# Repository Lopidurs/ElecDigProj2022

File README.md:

# ElecDigProj2022
Projet d'électronique digitale : Programmation d'un PIC18F458 pour mesurer une distance avec un HC-SR04

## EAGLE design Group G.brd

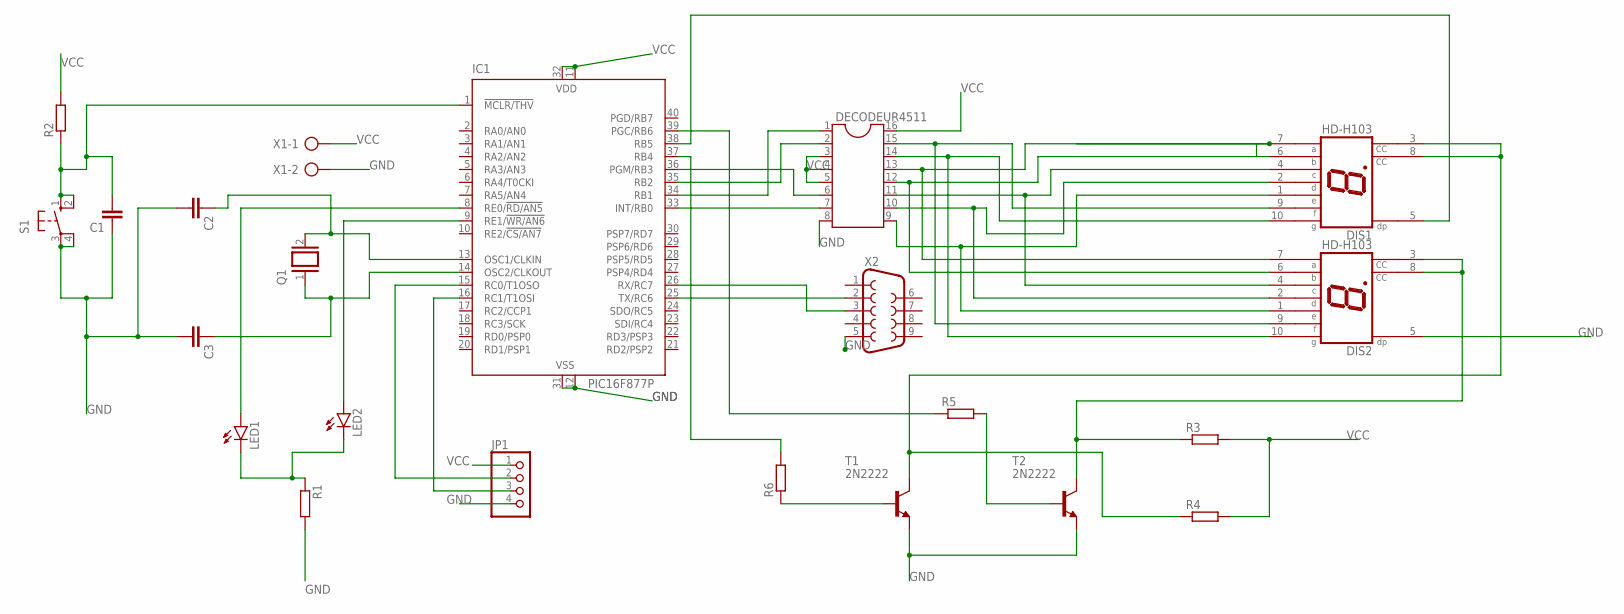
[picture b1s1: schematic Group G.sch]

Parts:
C1, C2, C3: C-EU025-025X050; C025-025X050
DECODEUR4511: DIL16
DIS1, DIS2: HD-H103; HDSP-M
IC1: PIC16F877P; DIL40
JP1: PINHD-1X4; 1X04
LED1, LED2: LED5MM
Q1: XTAL/S; QS
R1, R2, R3, R4, R5, R6: R-EU_0207/10; 0207/10
S1: 10-XX; B3F-10XX
T1, T2: 2N2222; TO18
X1: AK300/2
X2: F09H

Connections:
GND: C1.1, C2.2, C3.2, DECODEUR4511.8, DIS2.5 (DP), IC1.12 (VSS), IC1.31 (VSS), JP1.4, R1.2, S1.3, S1.4 (P1), T1.1 (E), T2.1 (E), X1.2, X2.5
unnamed: IC1.25 (TX/RC6), X2.2
unnamed: IC1.26 (RX/RC7), X2.3
unnamed: DECODEUR4511.7, IC1.33 (INT/RB0)
unnamed: DECODEUR4511.1, IC1.34 (RB1)
unnamed: DECODEUR4511.2, IC1.35 (RB2)
unnamed: DECODEUR4511.6, IC1.36 (PGM/RB3)
unnamed: DECODEUR4511.13, DIS1.7 (A), DIS2.7 (A)
unnamed: DECODEUR4511.15, DIS1.9 (F), DIS2.9 (F)
unnamed: DECODEUR4511.14, DIS1.10 (G), DIS2.10 (G)
unnamed: DECODEUR4511.10, DIS1.2 (D), DIS2.2 (D)
unnamed: DECODEUR4511.12, DIS1.6 (B), DIS2.6 (B)
unnamed: DECODEUR4511.11, DIS1.4 (C), DIS2.4 (C)
unnamed: DECODEUR4511.9, DIS1.1 (E), DIS2.1 (E)
unnamed: IC1.8 (RE0/!RD/AN5), LED1.A
unnamed: IC1.37 (RB4), R6.2
unnamed: R6.1, T1.2 (B)
unnamed: IC1.15 (RC0/T1OSO), JP1.2
unnamed: DIS1.5 (DP), IC1.38 (RB5)
unnamed: IC1.39 (PGC/RB6), R5.1
unnamed: R5.2, T2.2 (B)
unnamed: IC1.9 (RE1/!WR/AN6), LED2.A
unnamed: C1.2, IC1.1 (!MCLR/THV), R2.1, S1.1 (S), S1.2 (S1)
unnamed: IC1.16 (RC1/T1OSI), JP1.3
unnamed: C2.1, IC1.13 (OSC1/CLKIN), Q1.2
unnamed: C3.1, IC1.14 (OSC2/CLKOUT), Q1.1
unnamed: DIS1.3 (CC), DIS1.8 (CC), R4.1, T1.3 (C)
unnamed: DIS2.3 (CC), DIS2.8 (CC), R3.1, T2.3 (C)
unnamed: LED1.K (C), LED2.K (C), R1.1
VCC: DECODEUR4511.3, DECODEUR4511.4, DECODEUR4511.5, DECODEUR4511.16, IC1.11 (VDD), IC1.32 (VDD), JP1.1, R2.2, R3.2, R4.2, X1.1

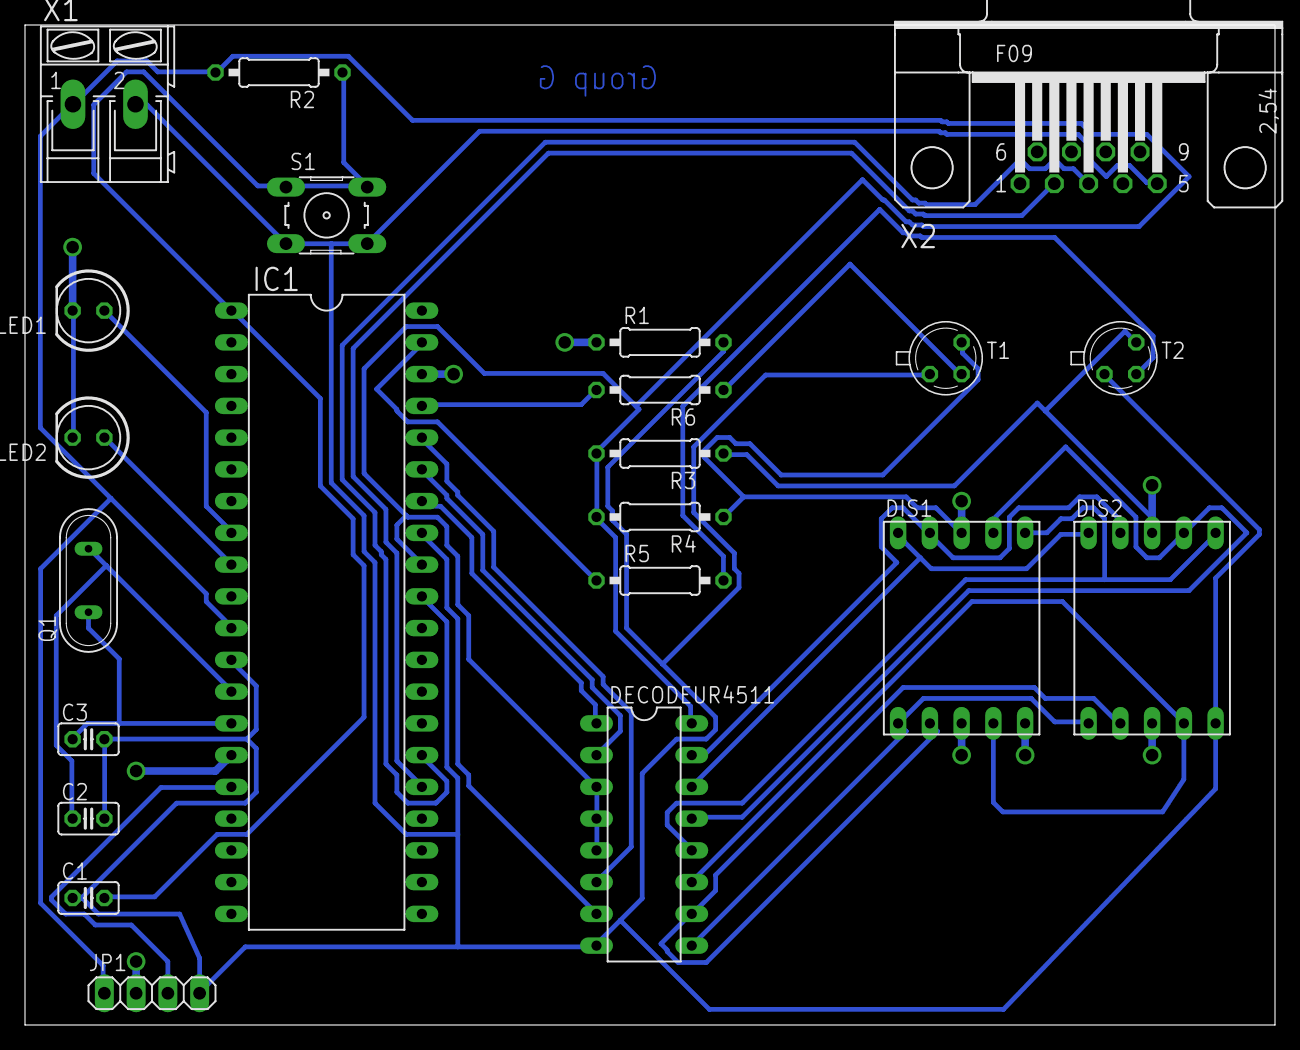
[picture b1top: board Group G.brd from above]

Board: 2 copper layers, 100.0 x 80.0 mm, 22 parts (0 on the bottom side), 30 nets.

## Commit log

2022-02-25 SCHÉMA PROTEUS
    Prototype du schéma
    Voici notre premier jet du projet d'electronique digitale.
2022-03-08 Mise au propre du schéma protheus. Remise du controle des afficheurs 7 segments sur deux pins. -> Evite d'ajouter des composants en plus (multiples portes not ou nand. On a tout de même assez de pins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
2022-03-09 Début schéma eagle
    Réalisé par Nathan Sancke avec l'aide de Jarod Boulanger-Flémal et le soutien de Raphaël Marto
2022-03-09 Correction du protheus. Les afficheurs 7 segments étaient en anode commune et pas cathodes communes. Ajout de la librairie protheus de la sonde à ultrasons. Ajout du code C. Gère pour le moment l'aff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
2022-03-11 Fichier schéma eagle
    Schéma eagle fini par Jarod Boulanger-Flémal.
2022-03-11 Schéma + Board eagle
    Schéma et board eagle réaliser par Jarod Boulanger-Flémal.
2022-03-11 delete untitled
    Suppression du fichier sans nom remplacer par le fichier nommé Groupe G
2022-03-11 Correction d'un branchement non fait + correction du nom du fichier (Goup B.brd -> Group B.brd)
2022-05-15 Ajout des fichier du programe c + schéma protéus de test
